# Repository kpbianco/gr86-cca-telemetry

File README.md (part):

# CCA Telemetry (GR86 / BRZ Gen2)

CCA Telemetry is a RaceChrono-compatible telemetry stack for the Toyota GR86 / Subaru BRZ (ZN8/ZD8) platform. An ESP32-S3 collects CAN, GPS, and auxiliary analog data, then streams it over Bluetooth Low Energy using RaceChrono's DIY device profile. The codebase is designed for track reliability: aggressive BLE reconnects, TWAI burst handling, persistent configuration, and configurable CAN filtering are all built in.

Hardware bring-up (CAN transceiver wiring, GPS, OLEDs, etc.) is intentionally out of scope here—assume those pieces are already handled. This repository focuses on the firmware, documentation, and validation artifacts you need to build, modify, and deploy the project.

## What this guide covers

* **End-to-end bring-up.** The “Track-day bring-up checklist” walks from flashing through wiring, BLE pairing, and pre-session validation so even a first-time CAN user can connect, configure, and verify the module before heading out.【F:README.md†L46-L125】
* **Subsystem deep dives.** “Firmware architecture,” “Oil pressure channel & calibration,” and the PID-map sections explain how each feature works (CAN ingest, BLE, GPS/PPS, oil analog path, pidmaps) and point directly to the source files for further hacking.【F:README.md†L77-L150】【F:README.md†L206-L213】
* **Runtime operations.** The Serial CLI reference documents every SHOW/PROFILE/ALLOW/FIL/TOKEN/RATE/SAVE command so you can administer the device without reflashing once it is installed in the car.【F:README.md†L214-L244】
* **RaceChrono & filtering workflows.** The RaceChrono integration, `.fil` ingestion walkthrough, and pidmap cloning guide teach you how to curate channels from the phone or at compile time, keeping CAN/BLE bandwidth under control.【F:README.md†L131-L150】【F:README.md†L180-L213】
* **Diagnostics & recovery.** LED pin/pattern tables, the troubleshooting checklist, and persistent-configuration guidance translate firmware counters into hands-on fixes at the car so you can recover from CAN, BLE, GPS, or oil faults mid-event.【F:README.md†L114-L130】【F:README.md†L123-L178】【F:README.md†L238-L244】

Together these sections document the full software feature set—from CAN filtering to RaceChrono streaming and oil calibration—so newcomers can treat the README as a production-ready operations guide.

## Release-ready polish

To make the repo publishable as an open-source reference design, every workflow called out in prior PRs is now paired with actionable guidance in this README:

* **Single source of truth.** The Track-day checklist, subsystem deep dives, CLI catalog, and RaceChrono workflows are all anchored to the implementation files they describe, so readers can jump from prose to code while auditing the feature set.
* **Operator focus.** Each runtime touch point—PID governance, GPS/PPS, oil calibration, RaceChrono filters, persistence—includes both “how it works” and “how to recover” instructions so someone new to CAN can confidently run the module at the track.
* **Debug-to-code breadcrumbs.** LED tables, SHOW/CAL output, and `.fil` logging now cite the handlers that emit those diagnostics, letting contributors trace symptoms back to the firmware without guesswork.

This section is the final assurance that the README stands alone as a production-ready operations manual: new users get the high-level tour at the top, the detailed workflows in the middle, and the debug/persistence references at the end without needing outside docs.

## Feature matrix & documentation coverage

| Feature / decision | Where it lives in code | Where to configure / operate it |
|--------------------|------------------------|----------------------------------|
| CAN burst ingestion, TWAI error recovery, PID throttling | `firmware/cca_telemetry.ino` main loop + TWAI handlers | *Firmware architecture → CAN ingestion & PID governance* and *Track-day bring-up checklist* describe how to wire and validate the bus before driving.【F:firmware/cca_telemetry.ino†L205-L235】【F:README.md†L23-L71】 |
| BLE transport, RaceChrono DIY profile, diagnostics notify | NimBLE setup in `firmware/cca_telemetry.ino` | *Track-day bring-up checklist → Pair with RaceChrono*, *RaceChrono integration*, and the troubleshooting bullets tie the LEDs, CLI, and `.fil` workflow together for new users.【F:firmware/cca_telemetry.ino†L89-L146】【F:README.md†L40-L73】【F:README.md†L120-L152】 |
| GPS + PPS time discipline | `firmware/src/gps_nmea.*`, PPS ISR in the sketch | *Firmware architecture → GPS & PPS discipline* plus the LED/troubleshooting tables walk through wiring, lock states, and debugging steps.【F:firmware/src/gps_nmea.cpp†L1-L210】【F:README.md†L75-L152】 |
| Oil pressure sampling, filtering, calibration, and CAN 0x710 publisher | Analog path in `firmware/cca_telemetry.ino` + `nvs_cfg.*` | *Track-day bring-up checklist*, *Oil pressure channel & calibration*, and the CLI section spell out how to hook up sensors, capture endpoints, and stream the data.【F:firmware/cca_telemetry.ino†L755-L807】【F:README.md†L33-L58】【F:README.md†L190-L225】 |
| PID maps, whitelist/deny list, divider overrides, `.fil` ingestion | `firmware/pidmaps/*.h`, filter characteristic handlers | *Creating your own PID map* and *Allowing extra PIDs from RaceChrono filter files* provide both build-time and runtime workflows, while CLI commands (`PROFILE`, `ALLOW`, `DENY`, `FIL VERBOSE`, `TOKEN`) are cataloged in the Serial CLI reference.【F:firmware/pidmaps/gr86_2022.h†L1-L162】【F:firmware/cca_telemetry.ino†L1360-L1465】【F:README.md†L152-L210】 |
| Persistent configuration and recovery | `firmware/src/nvs_cfg.*` | *Configuration workflow* and *Serial CLI → Persistence & recovery* explain how to edit defaults, capture runtime tweaks, and reset misconfigurations without reflashing.【F:firmware/src/nvs_cfg.cpp†L1-L116】【F:README.md†L171-L199】 |
| LED pinout, blink dictionary, scheduler hooks | `firmware/src/led_status.*`, `firmware/src/sched.hpp` | *Status LED + scheduler* table plus the troubleshooting checklist let a first-time CAN user translate physical indicators into next steps at the car.【F:firmware/src/led_status.cpp†L11-L192】【F:README.md†L92-L152】 |
| Build & flash repeatability | Arduino CLI/IDE instructions in this repo | *Building and flashing* covers both GUI and headless flows; the *Maintenance checklist* calls out regression tests to keep the repo production-ready.【F:README.md†L210-L266】 |

This matrix ensures every subsystem that ships in the firmware is paired with an operator-facing doc section, so a new builder can move from flashing through troubleshooting without chasing external resources.

## Repository layout

```
.
├── README.md                ← You're here
├── docs/                    ← RaceChrono presets and user-facing docs
├── firmware/
│   ├── cca_telemetry.ino    ← Main Arduino sketch for the ESP32-S3
│   ├── config.h             ← User-editable build-time configuration
│   ├── pidmaps/             ← CAN whitelist & scaling definitions
│   └── src/                 ← Reusable C++ helpers (GPS parser, NVS config, LEDs, scheduler)
├── libraries/               ← Vendored Arduino dependencies
```

## Track-day bring-up checklist

These steps walk a first-time CAN user from a blank ESP32-S3 dev module to a working RaceChrono feed. Each item links back to the source so you know which files implement the behavior you are validating.

### 1. Flash and configure the firmware

1. Install the ESP32 support package inside the Arduino IDE or CLI and select the **ESP32S3 Dev Module** target, matching the board the sketch was written for.【F:firmware/cca_telemetry.ino†L1-L20】
2. Open `firmware/config.h` and set the user-facing knobs—`DEVICE_NAME`, `DEFAULT_UPDATE_RATE_DIVIDER`, PPS input (`GPS_PPS_GPIO`), CAN baud, and `ACTIVE_PID_MAP`. These constants gate BLE discovery, the CAN throttle default, and whether PPS disciplining is enabled at boot.【F:firmware/config.h†L4-L27】
3. Build and flash `firmware/cca_telemetry.ino` using the instructions later in this README. The sketch pulls in the vendored libraries automatically, so no additional dependency fetch is required beyond what lives in `libraries/`.【F:firmware/cca_telemetry.ino†L21-L57】
4. Connect to the USB serial console at 115200 8N1, hit enter to reveal the prompt, then run `SHOW CFG` to confirm the compiled defaults (BLE name, profile mode, dividers) match what you edited before heading to the car.【F:firmware/cca_telemetry.ino†L2370-L2395】【F:firmware/cca_telemetry.ino†L3400-L3409】

### 2. Wire and power the module

1. Tie the SN65HVD230 (or equivalent) transceiver’s TXD/RXD pins to `GPIO5`/`GPIO4`, then hook its CANH/CANL pins into the car’s 500 kbps high-speed bus; the firmware leaves the TWAI controller in listen mode until it sees valid frames so you can verify the connection on the bench first.【F:firmware/cca_telemetry.ino†L76-L82】【F:firmware/config.h†L20-L21】
2. Wire your GPS puck to UART1 (`GPIO18` ← GPS TX, `GPIO17` → GPS RX) and land an optional PPS input on `GPIO16` if you want nanosecond-level lap timing—the PPS ISR and slew limiter are already enabled as soon as `GPS_PPS_GPIO` is ≥ 0.【F:firmware/cca_telemetry.ino†L80-L109】【F:firmware/config.h†L11-L15】
3. Route the analog oil-pressure sender into `GPIO1/ADC1_CH0`. The firmware samples, filters, and publishes it on virtual CAN ID `0x710`, so all you need to do trackside is capture two calibration points with the CLI after plumbing the sensor.【F:firmware/cca_telemetry.ino†L5-L7】【F:firmware/cca_telemetry.ino†L755-L775】
4. Land the status LEDs on the default pins (`GPIO46`, `GPIO6`, `GPIO7`, `GPIO8`, `GPIO10`, and `GPIO3`) or adjust the macros in `firmware/src/led_status.h` if your harness is different. The table later in this README explains every blink pattern you will see once the car powers the unit.【F:firmware/src/led_status.h†L6-L32】【F:firmware/cca_telemetry.ino†L1368-L1373】

### 3. Pair with RaceChrono and feed channels

1. Power the car or bench supply so the ESP32 starts advertising under the `DEVICE_NAME` you configured. RaceChrono will discover the DIY service (`0x1FF8`) plus the CAN, GPS, GPS-time, filter, and diagnostics characteristics defined in the sketch.【F:firmware/cca_telemetry.ino†L89-L95】
2. Import `docs/racechrono_preset.md` into RaceChrono to create ready-made channels for every GR86/BRZ PID in the curated allow-list, including the synthetic oil frame on `0x710`. This saves you from typing scaling equations on the phone.【F:docs/racechrono_preset.md†L1-L68】
3. If you need to add or remove CAN IDs directly from your phone, issue a `TOKEN <hex8>` over serial and then push a `.fil` file from RaceChrono’s *Manage filters* UI. Each command in the file becomes an ALLOW/DENY write on characteristic `0x0002`, which the firmware authenticates with the token before applying it to the runtime map.【F:firmware/cca_telemetry.ino†L1360-L1465】【F:firmware/cca_telemetry.ino†L3613-L3647】
4. Finish the pairing pass by checking `SHOW MAP` / `SHOW DENY` and the BLE diagnostics characteristic (`0x0005`) so you know the RaceChrono UI and the firmware are in sync before the session.【F:firmware/cca_telemetry.ino†L3345-L3505】【F:firmware/cca_telemetry.ino†L867-L920】

### 4. Validate data flow and hit the track

1. Watch the LED bank: solid power LED plus pulsing CAN/GPS LEDs indicate the car is broadcasting and GPS sentences are flowing, while the SYS LED warns about BLE throttling so you can bump dividers before packets drop.【F:firmware/src/led_status.h†L6-L32】【F:firmware/cca_telemetry.ino†L3732-L3879】
2. Use `SHOW STATS` after a shakedown lap to confirm there are no CAN timeouts, TWAI restarts, or BLE notify drops. The counters cover every subsystem mentioned earlier in this README.【F:firmware/cca_telemetry.ino†L3411-L3438】
3. Run `CAL SHOW`, `SHOW CFG`, and `RATE` to double-check that oil calibration, broadcast cadence, and profile mode match what you expect before logging laps; save any runtime tweaks so they persist across pit cycles.【F:firmware/cca_telemetry.ino†L3507-L3575】【F:firmware/cca_telemetry.ino†L3566-L3575】【F:firmware/cca_telemetry.ino†L782-L807】

## Firmware architecture

The sketch in `firmware/cca_telemetry.ino` orchestrates several subsystems:

* **CAN ingestion** – `ESP32-TWAI-CAN` runs the ESP32's native TWAI controller in RX burst mode. PID throttling keeps BLE bandwidth under control while the `pidmaps` whitelist ensures only RaceChrono-ready signals are forwarded.
* **BLE transport** – `NimBLE-Arduino` implements the RaceChrono DIY profile (service `0x1FF8`). Notifications are rate-limited with an adaptive governor, reconnection restarts advertisers instead of destroying the controller, and diagnostic counters identify congestion/backpressure.
* **GPS & PPS discipline** – `firmware/src/gps_nmea.*` parses RMC/GGA sentences and disciplines system time to an external PPS input with slew limiting.
* **Persistent configuration** – `firmware/src/nvs_cfg.*` stores calibration data (analog dividers, device profile, etc.) in NVS so tweaks survive power cycles.
* **Status LED + scheduler** – `firmware/src/led_status.*` and `firmware/src/sched.hpp` provide non-blocking indicators and lightweight cooperative task scheduling for housekeeping loops.
* **RaceChrono mapping** – `firmware/pidmaps/` encapsulates CAN scaling/units per signal. `config.h` selects the active table and exposes knobs such as BLE device name, update dividers, and analog calibration constants.

### Subsystem deep dive

#### CAN ingestion and PID governance

The CAN stack configures TWAI alerts for RX queue overruns, bus-off, arbitration loss, and other critical faults, then polls those counters each second to decide when to restart the controller or surface diagnostic frames back to RaceChrono.【F:firmware/cca_telemetry.ino†L205-L235】 Above that, the `pidmaps` layer predefines the GR86/BRZ whitelist plus default per-ID dividers and lets the CLI flip between strict allow-list streaming (`PROFILE ON`) or a sniff-all fall-through that still honors the runtime deny list.【F:firmware/pidmaps/gr86_2022.h†L9-L118】【F:firmware/cca_telemetry.ino†L718-L865】 Custom divider overrides are persisted and applied on boot so you can bump individual CAN IDs without recompiling, and the same bookkeeping powers `SHOW MAP`, `ALLOW`, and `DENY` in the serial console.【F:firmware/cca_telemetry.ino†L712-L865】【F:firmware/cca_telemetry.ino†L3345-L3505】

**Whitelist, blacklist, and dividers.** Each entry in `firmware/pidmaps/*.h` carries a target RaceChrono channel plus a default divider, meaning “forward one in every _N_ frames for this CAN ID.” Lower dividers increase BLE load; higher ones conserve bandwidth for low-value or high-frequency signals. `PROFILE ON` enforces this whitelist (only IDs present in the map are forwarded) while `PROFILE OFF` switches to “sniff everything” and relies on the deny list to suppress noisy IDs. `ALLOW <pid> <div>` temporarily whitelists additional IDs with their own dividers, whereas `DENY <pid>` forces the firmware to drop that ID even if the profile is off or the ID appears in the static map. Both overrides are stored in NVS via `SAVE` so trackside experiments persist across reboots.【F:firmware/cca_telemetry.ino†L3341-L3609】

#### BLE transport and congestion control

`NimBLE-Arduino` exposes the full DIY profile (CAN, filter, GPS, GPS time, and diagnostics characteristics) and negotiates aggressive 7.5–15 ms connection intervals to keep RaceChrono synced.【F:firmware/cca_telemetry.ino†L275-L357】 A moving-average notify governor tracks bytes-per-second, clamps burst size, and progressively backs off when congestion or ATT errors show up, with event counters logged through `SHOW STATS` and the diagnostics characteristic so you know whether BLE or CAN is the bottleneck.【F:firmware/cca_telemetry.ino†L139-L174】【F:firmware/cca_telemetry.ino†L867-L920】 The reconnection path restarts advertisers and reapplies MTU sizing automatically, so unplugging power or losing the phone link no longer wedges the NimBLE host.【F:firmware/cca_telemetry.ino†L301-L357】

#### GPS and PPS discipline

`gps_nmea.cpp` parses both RMC and GGA sentences, clamps checksum errors, and normalizes latitude/longitude/altitude fields, while the main sketch tracks the GPS init state machine (autobaud probing, fallback timers, and periodic notify cadence).【F:firmware/src/gps_nmea.cpp†L1-L121】【F:firmware/src/gps_nmea.cpp†L123-L198】【F:firmware/cca_telemetry.ino†L237-L274】 When a PPS input is wired, the ISR debounces the pulse, estimates drift, and slews the system clock by ±2 ms/second to keep RaceChrono’s GPS and CAN timestamps aligned, which dramatically reduces lap interpolation error.【F:firmware/cca_telemetry.ino†L176-L188】

#### Persistent configuration and CLI tie-in

The `nvs_cfg` helpers serialize oil calibration voltages, versioning, and CRCs into the `cca_cfg` namespace so even power-cycled cars retain the analog slope you captured with `CAL` commands.【F:firmware/src/nvs_cfg.cpp†L1-L75】 Raw blobs can be inspected with `CAL SHOW`, and the same module exposes guard rails (finite, monotonic voltages) to keep corrupt data from applying at boot.【F:firmware/src/nvs_cfg.cpp†L76-L116】 In addition to analog endpoints, NVS stores PID divider overrides, custom oil broadcast rates, FIL tokens, and the profile bit so the CLI “SAVE / LOAD / RESETCFG” workflow mirrors what’s burned into flash.【F:firmware/cca_telemetry.ino†L782-L865】【F:firmware/cca_telemetry.ino†L3650-L3674】

#### Status LED + scheduler

`led_status.*` defines six independent channels (power, BLE, CAN, GPS, SYS, oil) with per-pin polarity, a library of blink/pulse patterns, and a tiny state machine that updates the GPIOs without blocking other tasks.【F:firmware/src/led_status.cpp†L11-L192】 Time-sliced housekeeping loops use the `every()` helper in `sched.hpp` to run at deterministic cadences (GPS notify, CAN diagnostics, oil broadcasts) even when other work momentarily stalls the main loop.【F:firmware/src/sched.hpp†L5-L23】

**Pinout and debug patterns.** The default harness routes the LEDs to the following ESP32-S3 pins (active high unless the macros in `led_status.h` are flipped). Use the table to translate each blink or pulse into a subsystem status when debugging at the car.【F:firmware/src/led_status.h†L6-L53】【F:firmware/cca_telemetry.ino†L1368-L1373】【F:firmware/cca_telemetry.ino†L3740-L3887】

| LED | ESP32-S3 GPIO | Patterns & meaning |
|-----|---------------|---------------------|
| Power | `GPIO46` | Turns solid immediately after `setup()` runs so you know the MCU left ROM boot and the scheduler/housekeeping loops are alive.【F:firmware/src/led_status.h†L6-L22】【F:firmware/cca_telemetry.ino†L2370-L2384】 |
| BLE | `GPIO6` | Fast blink while advertising/awaiting RaceChrono, solid once a BLE link is up, and off once RaceChrono disconnects so you can instantly spot pairing issues.【F:firmware/src/led_status.h†L6-L24】【F:firmware/cca_telemetry.ino†L1368-L1373】 |
| CAN | `GPIO7` | Slow blink means the TWAI driver is up but no recent frames have been seen, a double pulse every 2 s indicates live CAN traffic, and solid means the reader is running but has gone >1 s without a packet (check wiring or ignition).【F:firmware/src/led_status.h†L6-L26】【F:firmware/cca_telemetry.ino†L3732-L3744】 |
| GPS | `GPIO8` | Slow blink while waiting on UART data, solid when NMEA sentences are flowing, and triple pulses every two seconds once valid RMC fixes are locking timestamps to PPS.【F:firmware/src/led_status.h†L6-L28】【F:firmware/cca_telemetry.ino†L3860-L3875】 |
| SYS | `GPIO10` | Off during normal operation; switches to a slow blink whenever the BLE governor clamps notifications or the burst budget is exhausted, highlighting congestion before packets drop.【F:firmware/src/led_status.h†L6-L30】【F:firmware/cca_telemetry.ino†L3778-L3879】 |
| Oil | `GPIO3` | Solid = calibrated sensor in range; fast blink = ADC sees a short to ground; double pulse every 2 s = open harness; slow blink = voltage out of range but not a hard fault, matching the fault bits that go out on CAN `0x710`.【F:firmware/src/led_status.h†L6-L32】【F:firmware/cca_telemetry.ino†L3838-L3849】 |

## Troubleshooting checklist

* **No CAN frames** – Verify the CAN LED is double-pulsing; if it is solid or dark, check the SN65 wiring on `GPIO5/4` and make sure the bus really is at 500 kbps, then run `SHOW STATS` to confirm there are no TWAI restarts or RX timeouts being logged.【F:firmware/cca_telemetry.ino†L76-L82】【F:firmware/config.h†L20-L21】【F:firmware/cca_telemetry.ino†L3411-L3438】
* **BLE congestion** – A blinking SYS LED means the notify governor is clamping bursts; inspect the diagnostics characteristic (`0x0005`) and `SHOW STATS` counters, then raise the per-PID dividers or disable noisy IDs via `DENY`/`ALLOW`/`PROFILE` until the clamp counter stabilizes.【F:firmware/src/led_status.h†L6-L30】【F:firmware/cca_telemetry.ino†L867-L920】【F:firmware/cca_telemetry.ino†L3341-L3609】
* **GPS not locking** – The GPS LED should switch from slow blink to solid once UART sentences arrive and to triple pulses when PPS discipline is active; if it stays dark, confirm the UART pins (`GPIO18/17`) and PPS input (`GPIO16`) match your harness and recheck the GPS baud/autobaud logic in the console output.【F:firmware/cca_telemetry.ino†L80-L188】【F:firmware/config.h†L11-L15】【F:firmware/src/led_status.h†L6-L28】
* **Oil channel faults** – Combine the oil LED pattern with `CAL SHOW` output to see whether you are tripping the open/short bits, broadcasting stale calibration endpoints, or simply exceeding the configured pressure range. `RATE` lets you slow the cadence if BLE saturation coincides with the faults.【F:firmware/cca_telemetry.ino†L3382-L3549】【F:firmware/cca_telemetry.ino†L3566-L3575】【F:firmware/src/led_status.h†L6-L32】
* **RaceChrono filters not applying** – Turn `FIL VERBOSE ON`, make sure the FIL token matches, and watch the serial console for ALLOW/DENY updates while the `.fil` file streams; the runtime state is always visible via `SHOW MAP` / `SHOW DENY` before you `SAVE`.【F:firmware/cca_telemetry.ino†L1360-L1465】【F:firmware/cca_telemetry.ino†L3345-L3655】

#### RaceChrono mapping & docs

`firmware/pidmaps/` centralizes the RaceChrono-facing whitelist, scaling equations, and default dividers so each CAN signal documents its frequency and equation in one place, and the `docs/racechrono_preset.md` file provides copy/paste RaceChrono channel definitions—including the virtual oil pressure frame—for anyone replicating the setup without reverse-engineering the CAN bus themselves.【F:firmware/pidmaps/gr86_2022.h†L9-L162】【F:docs/racechrono_preset.md†L1-L68】

### Creating your own PID map

1. **Copy the template.** Duplicate `firmware/pidmaps/gr86_2022.h`, keep the include to `pidmaps/pidmap_defs.h`, and rename the namespace/`MAP` constant to match your chassis so the compiler gets a unique `PidMapDefinition`. The header already shows how the whitelist helper, divider policy, and `RULES` array hang together.【F:firmware/pidmaps/pidmap_defs.h†L1-L24】【F:firmware/pidmaps/gr86_2022.h†L1-L106】
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
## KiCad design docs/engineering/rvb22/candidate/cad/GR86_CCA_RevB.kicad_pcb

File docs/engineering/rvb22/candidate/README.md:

# GR86 Rev B — I12 corrective engineering in progress

The upper PCB wing now carries the approved compact TranquilWorks TW artwork in one-color silkscreen. The U201 library antenna rule area is corrected from board-relative translation to local coordinates; the board keepout and all electrical geometry remain unchanged. All153 fitted references have model references;22 missing/broken entries receive dimensioned envelopes with explicit XY and height provenance. Native export coverage is now checked against all153 STEP assembly occurrences.

This is an intermediate checkpoint within the coordinated I12 revision. Thermal, foil/contact, complete connector envelopes and affected regressions remain in progress, as listed in verification/I12/REDLINE_FREEZE.json. Native reevaluation is pending; no release or zero-overall claim follows from these edits.

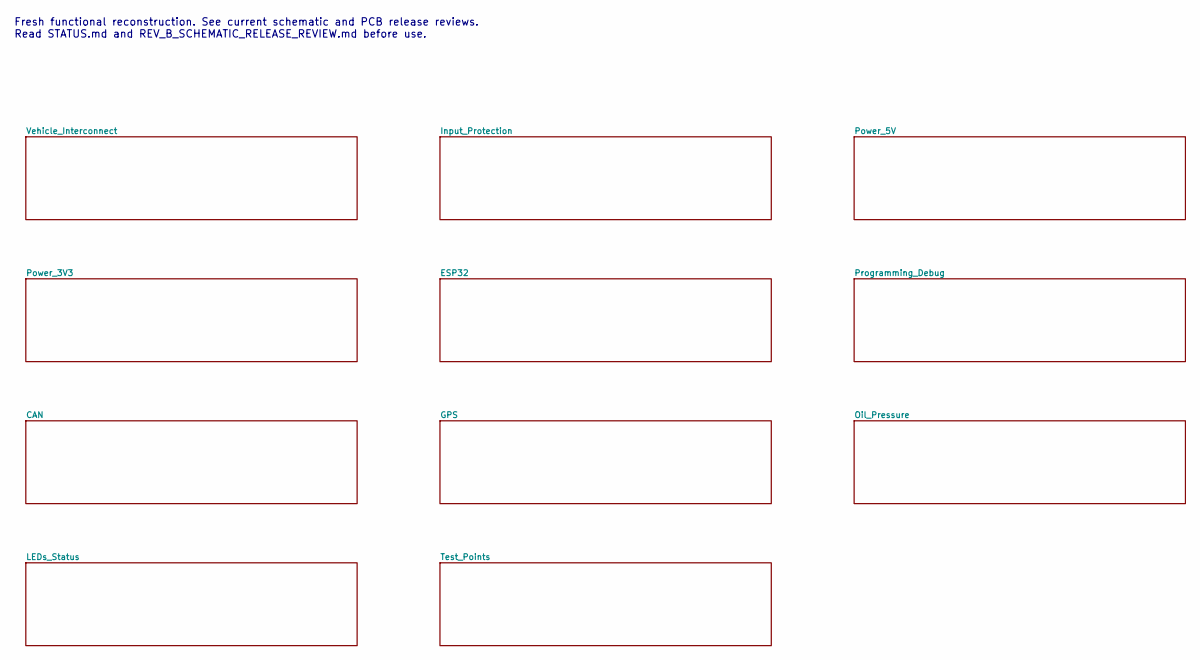
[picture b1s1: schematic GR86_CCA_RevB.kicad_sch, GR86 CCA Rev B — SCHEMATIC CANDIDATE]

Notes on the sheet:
Fresh functional reconstruction. See current schematic and PCB release reviews. Read STATUS.md and REV_B_SCHEMATIC_RELEASE_REVIEW.md before use.

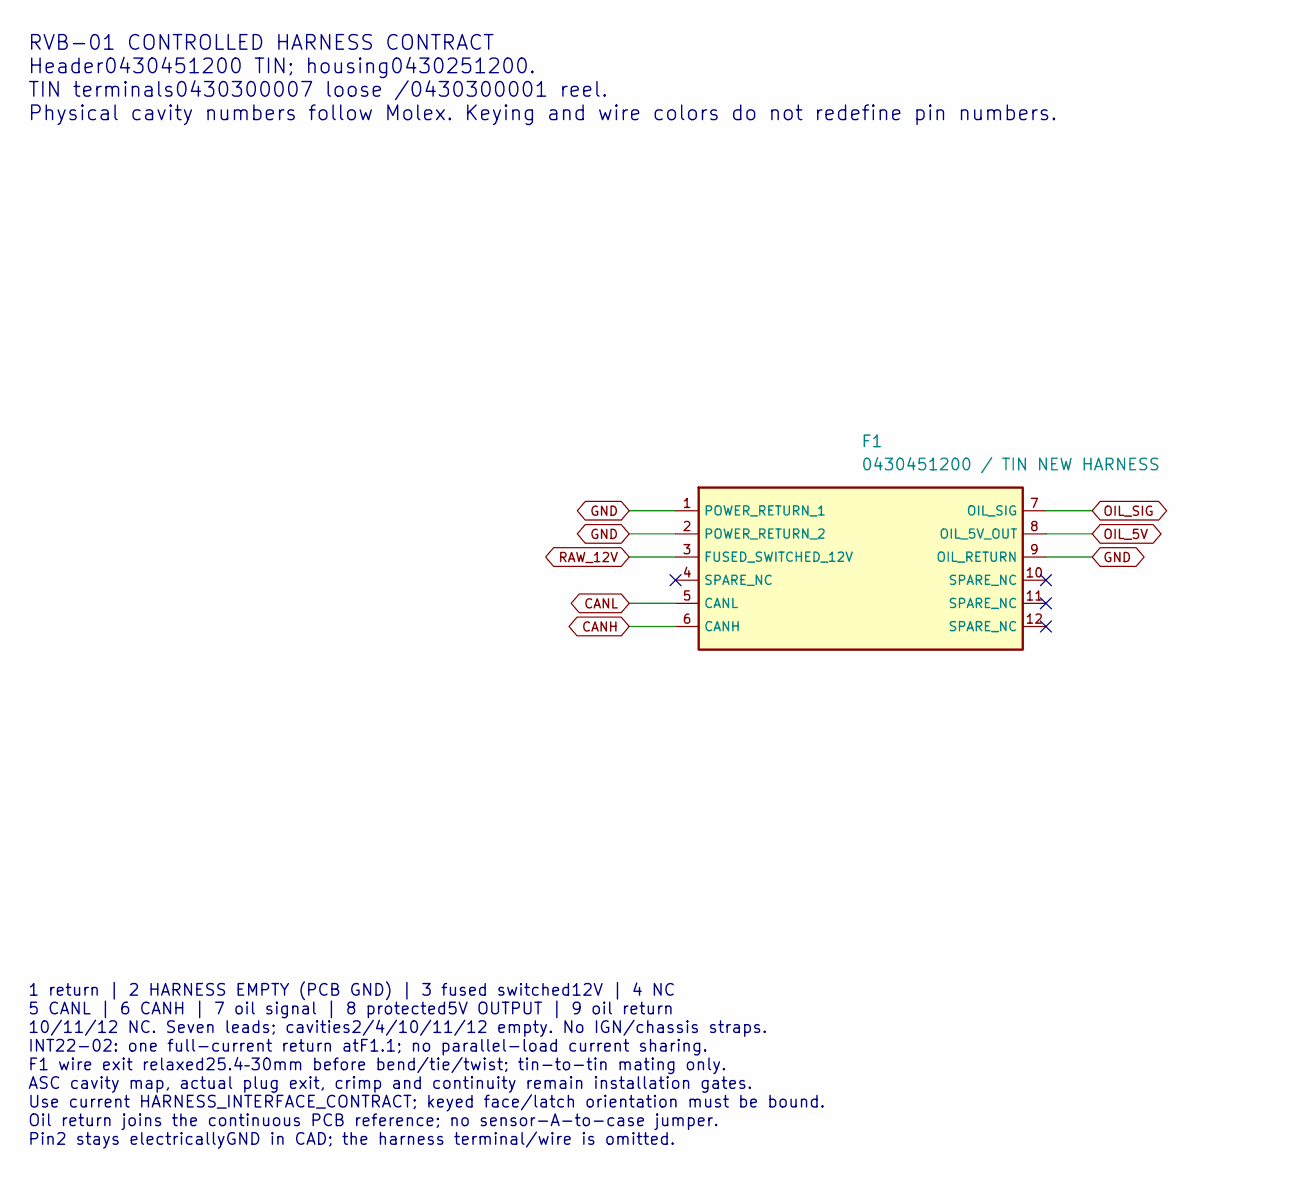
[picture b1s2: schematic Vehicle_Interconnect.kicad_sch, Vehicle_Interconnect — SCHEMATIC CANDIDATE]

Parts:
F1: 0430451200 / TIN NEW HARNESS; Molex_Micro-Fit_3.0_43045-1200_2x06_P3.00mm_Horizontal_RVB2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; MPN 0430451200; LCSC C277636

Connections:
CANH: F1.6 (CANH); also elsewhere on the board
CANL: F1.5 (CANL); also elsewhere on the board
GND: F1.1 (POWER_RETURN_1), F1.2 (POWER_RETURN_2), F1.9 (OIL_RETURN); also elsewhere on the board
OIL_5V: F1.8 (OIL_5V_OUT); also elsewhere on the board
OIL_SIG: F1.7 (OIL_SIG); also elsewhere on the board
RAW_12V: F1.3 (FUSED_SWITCHED_12V); also elsewhere on the board

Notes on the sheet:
RVB-01 CONTROLLED HARNESS CONTRACT Header0430451200 TIN; housing0430251200. TIN terminals0430300007 loose /0430300001 reel. Physical cavity numbers follow Molex. Keying and wire colors do not redefine pin numbers.
1 return | 2 HARNESS EMPTY (PCB GND) | 3 fused switched12V | 4 NC 5 CANL | 6 CANH | 7 oil signal | 8 protected5V OUTPUT | 9 oil return 10/11/12 NC. Seven leads; cavities2/4/10/11/12 empty. No IGN/chassis straps. INT22-02: one full-current return atF1.1; no parallel-load current sharing. F1 wire exi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

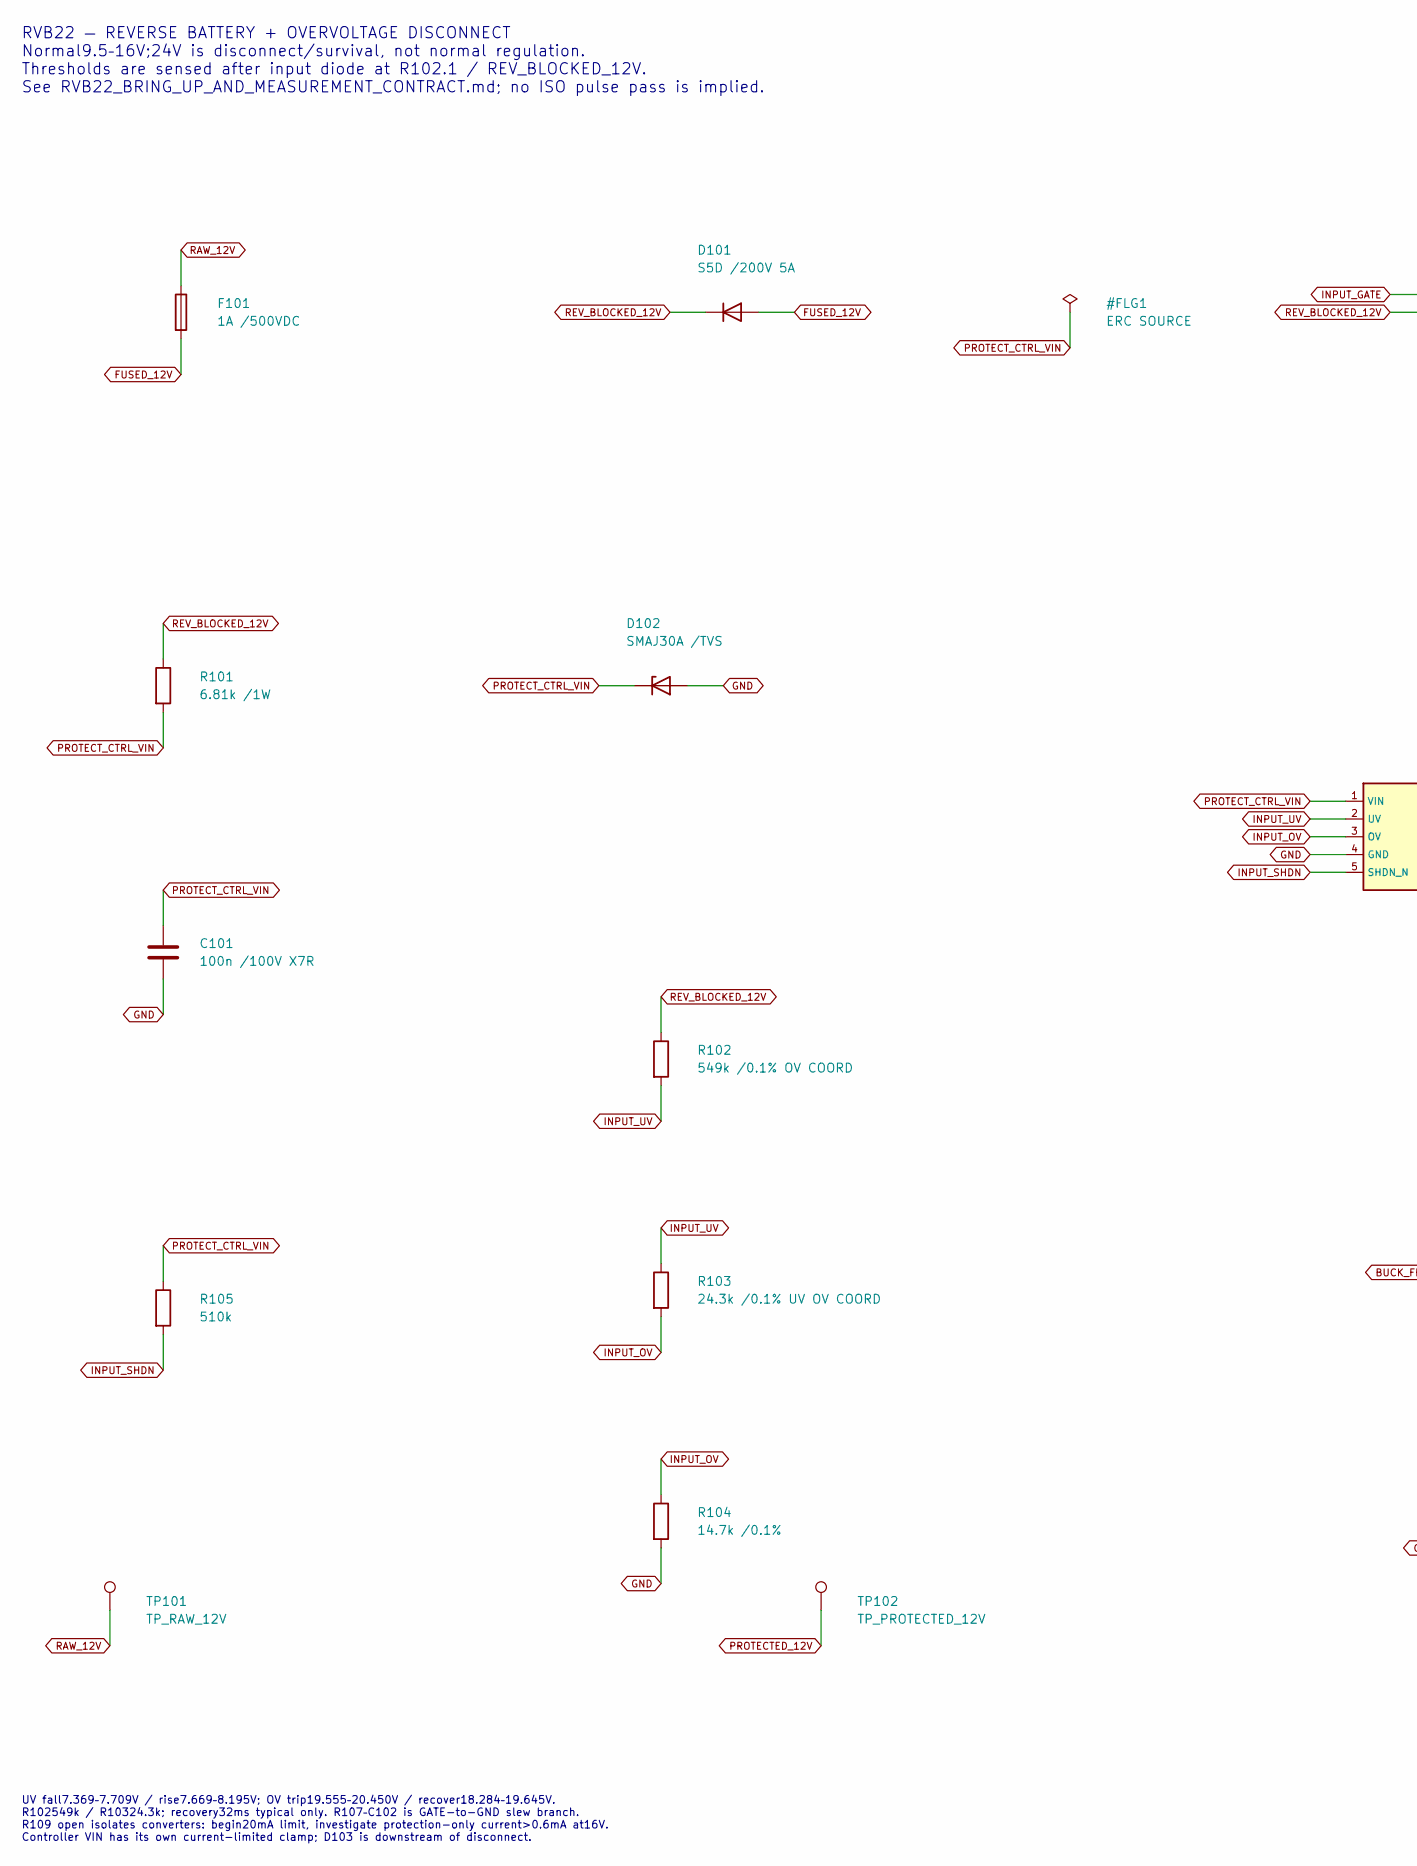
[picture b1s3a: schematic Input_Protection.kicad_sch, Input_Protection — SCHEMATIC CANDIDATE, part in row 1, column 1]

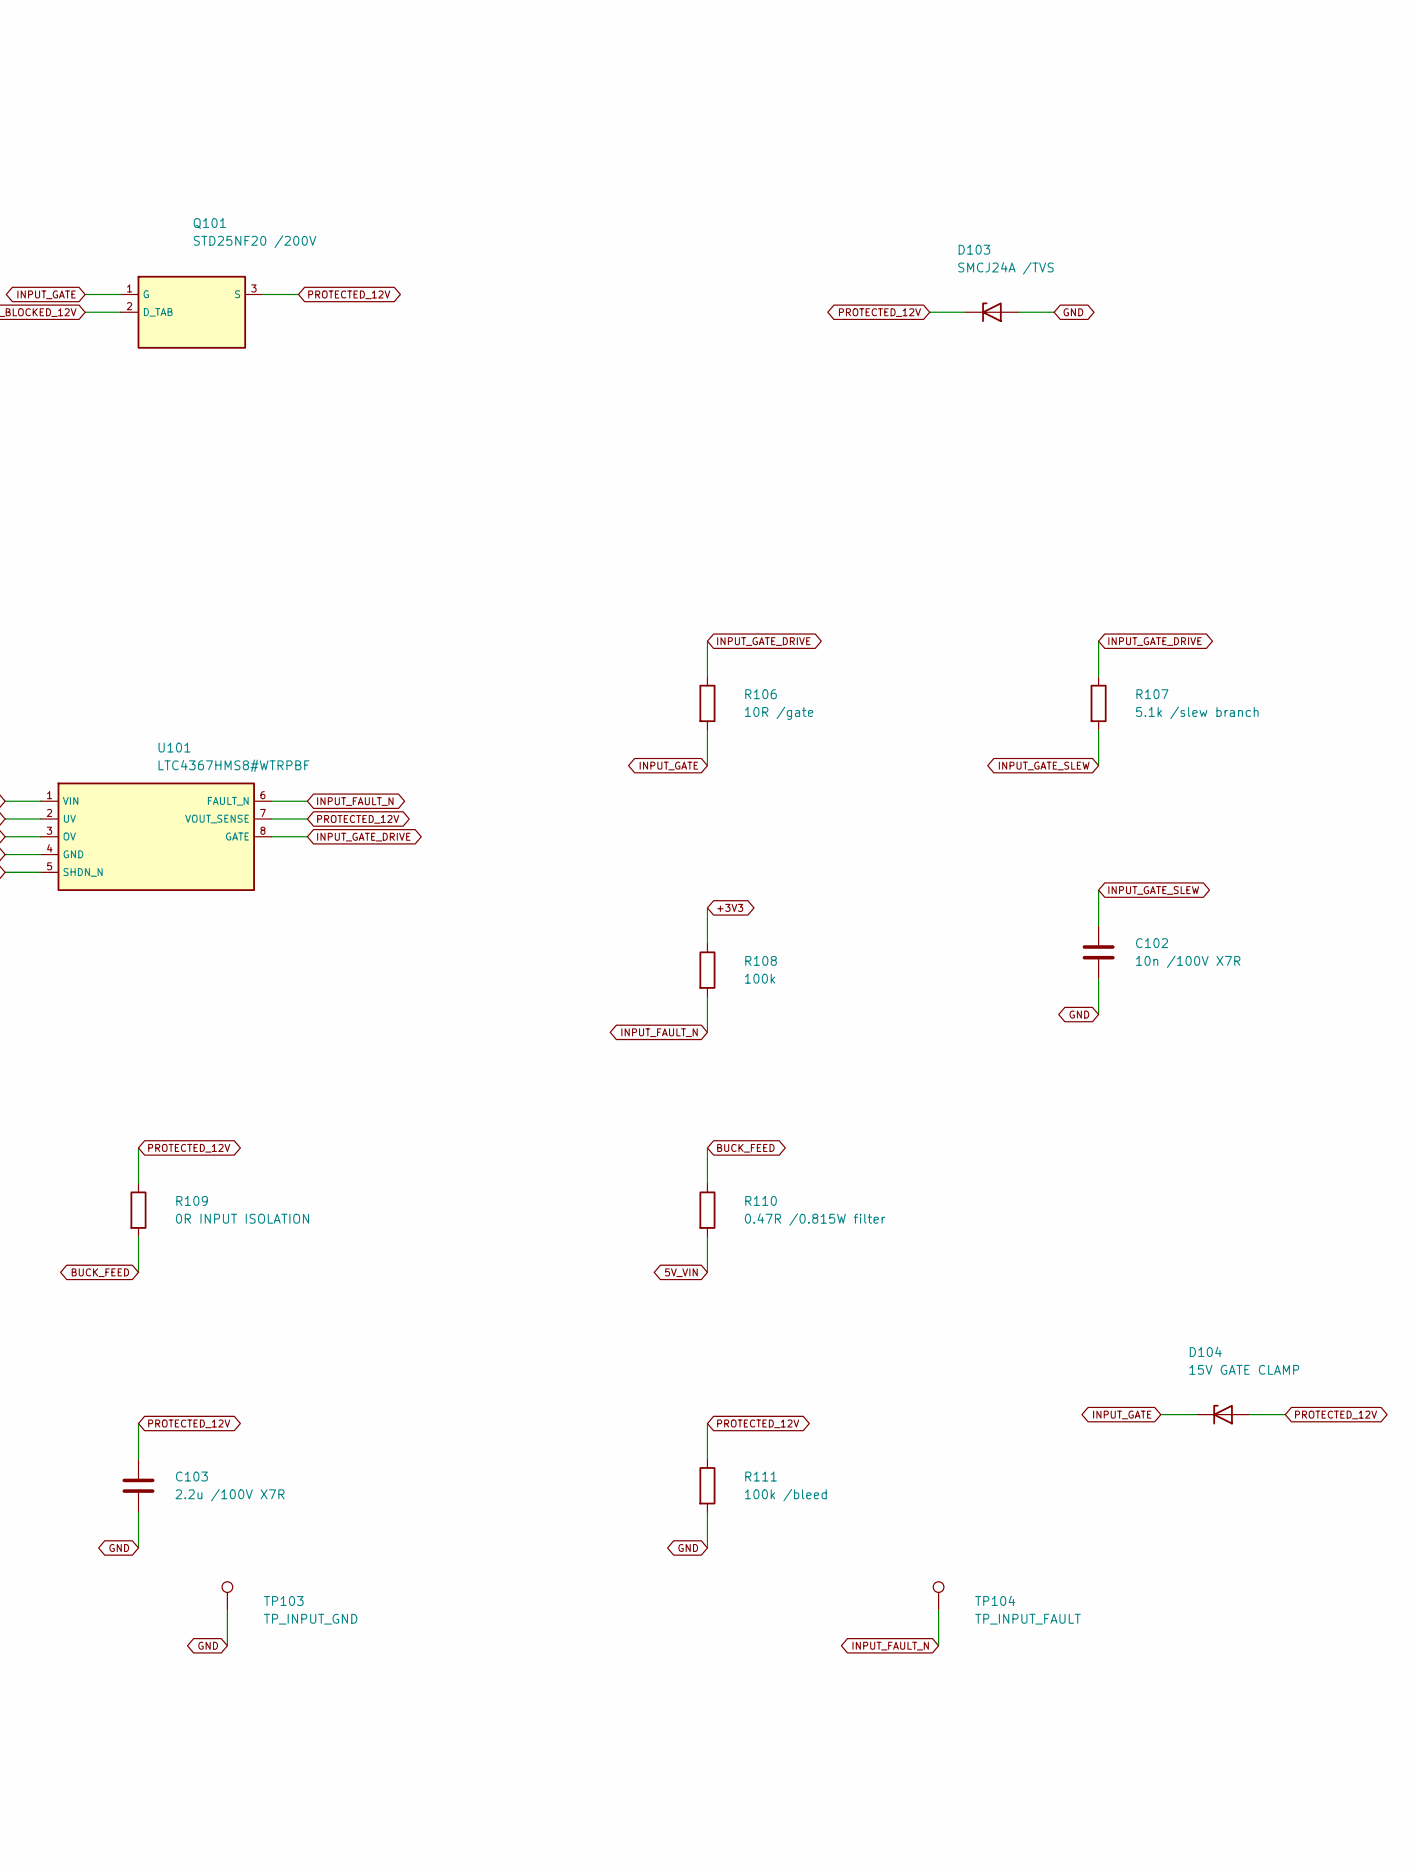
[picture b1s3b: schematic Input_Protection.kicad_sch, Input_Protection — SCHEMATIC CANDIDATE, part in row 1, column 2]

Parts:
C101: 100n /100V X7R; C_0805_2012Metric; MPN CGA4J2X7R2A104K125AA; LCSC C342919
C102: 10n /100V X7R; C_0603_1608Metric; MPN CGA3E2X7R2A103K080AE; LCSC C3858696
C103: 2.2u /100V X7R; C_1210_3225Metric; MPN CGA6N3X7R2A225K230AB; LCSC C342652
D101: S5D /200V 5A; D_SMC; MPN S5DHE3_A/H; LCSC C17442489
D102: SMAJ30A /TVS; D_SMA; MPN SMAJ30AHE3_A/H; LCSC C1978408
D103: SMCJ24A /TVS; D_SMC_RVB22_D103; MPN SMCJ24AHE3_A/H; LCSC C1981952
D104: 15V GATE CLAMP; D_SOD-123F; MPN BZT52H-B15-QX; LCSC C7507926
F101: 1A /500VDC; Fuse_Littelfuse-NANO2-885; MPN 0885001.DR; LCSC C2879865
Q101: STD25NF20 /200V; TO-252-2; MPN STD25NF20; LCSC C388326
R101: 6.81k /1W; R_2512_6332Metric; MPN CRCW25126K81FKEG; LCSC C4207450
R102: 549k /0.1% OV COORD; R_1206_3216Metric; MPN TNPW1206549KBEEA
R103: 24.3k /0.1% UV OV COORD; R_0603_1608Metric; MPN TNPW060324K3BEEA
R104: 14.7k /0.1%; R_0603_1608Metric; MPN ERA3AEB1472V; LCSC C2074591
R105: 510k; R_1206_3216Metric; MPN CRCW1206510KFKEA; LCSC C843859
R106: 10R /gate; R_0603_1608Metric; MPN CRCW060310R0FKEA; LCSC C844919
R107: 5.1k /slew branch; R_0603_1608Metric; MPN CRCW06035K10FKEA; LCSC C844933
R108: 100k; R_0603_1608Metric; MPN CRCW0603100KFKEA; LCSC C844916
R109: 0R INPUT ISOLATION; R_1206_3216Metric; MPN CRCW12060000Z0EA; LCSC C190124
R110: 0.47R /0.815W filter; R_2512_6332Metric; MPN WSL2512R4700FEA; LCSC C4273015
R111: 100k /bleed; R_1206_3216Metric; MPN CRCW1206100KFKEA; LCSC C844863
TP101: TP_RAW_12V; TestPoint_Pad_D1.5mm; MPN BARE PCB PAD
TP102: TP_PROTECTED_12V; TestPoint_Pad_D1.5mm; MPN BARE PCB PAD
TP103: TP_INPUT_GND; TestPoint_Pad_D1.5mm; MPN BARE PCB PAD
TP104: TP_INPUT_FAULT; TestPoint_Pad_D1.5mm; MPN BARE PCB PAD
U101: LTC4367HMS8#WTRPBF; MSOP-8_3x3mm_P0.65mm; MPN LTC4367HMS8#WTRPBF

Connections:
5V_VIN: R110.2; also elsewhere on the board
+3V3: R108.1; also elsewhere on the board
BUCK_FEED: R109.2, R110.1
FUSED_12V: D101.2 (A), F101.2
GND: C101.2, C102.2, C103.2, D102.2 (A), D103.2 (A), R104.2, R111.2, TP103.1, U101.4 (GND); also elsewhere on the board
INPUT_FAULT_N: R108.2, TP104.1, U101.6 (FAULT_N)
INPUT_GATE: D104.1 (K), Q101.1 (G), R106.2
INPUT_GATE_DRIVE: R106.1, R107.1, U101.8 (GATE)
INPUT_GATE_SLEW: C102.1, R107.2
INPUT_OV: R103.2, R104.1, U101.3 (OV)
INPUT_SHDN: R105.2, U101.5 (SHDN_N)
INPUT_UV: R102.2, R103.1, U101.2 (UV)
PROTECTED_12V: C103.1, D103.1 (K), D104.2 (A), Q101.3 (S), R109.1, R111.1, TP102.1, U101.7 (VOUT_SENSE)
PROTECT_CTRL_VIN: C101.1, D102.1 (K), R101.2, R105.1, U101.1 (VIN)
RAW_12V: F101.1, TP101.1; also elsewhere on the board
REV_BLOCKED_12V: D101.1 (K), Q101.2 (D_TAB), R101.1, R102.1

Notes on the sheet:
RVB22 — REVERSE BATTERY + OVERVOLTAGE DISCONNECT Normal9.5–16V;24V is disconnect/survival, not normal regulation. Thresholds are sensed after input diode at R102.1 / REV_BLOCKED_12V. See RVB22_BRING_UP_AND_MEASUREMENT_CONTRACT.md; no ISO pulse pass is implied.
UV fall7.369–7.709V / rise7.669–8.195V; OV trip19.555–20.450V / recover18.284–19.645V. R102549k / R10324.3k; recovery32ms typical only. R107–C102 is GATE-to-GND slew branch. R109 open isolates converters: begin20mA limit, investigate protection-only current>0.6mA at16V. Controller VIN has its own c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

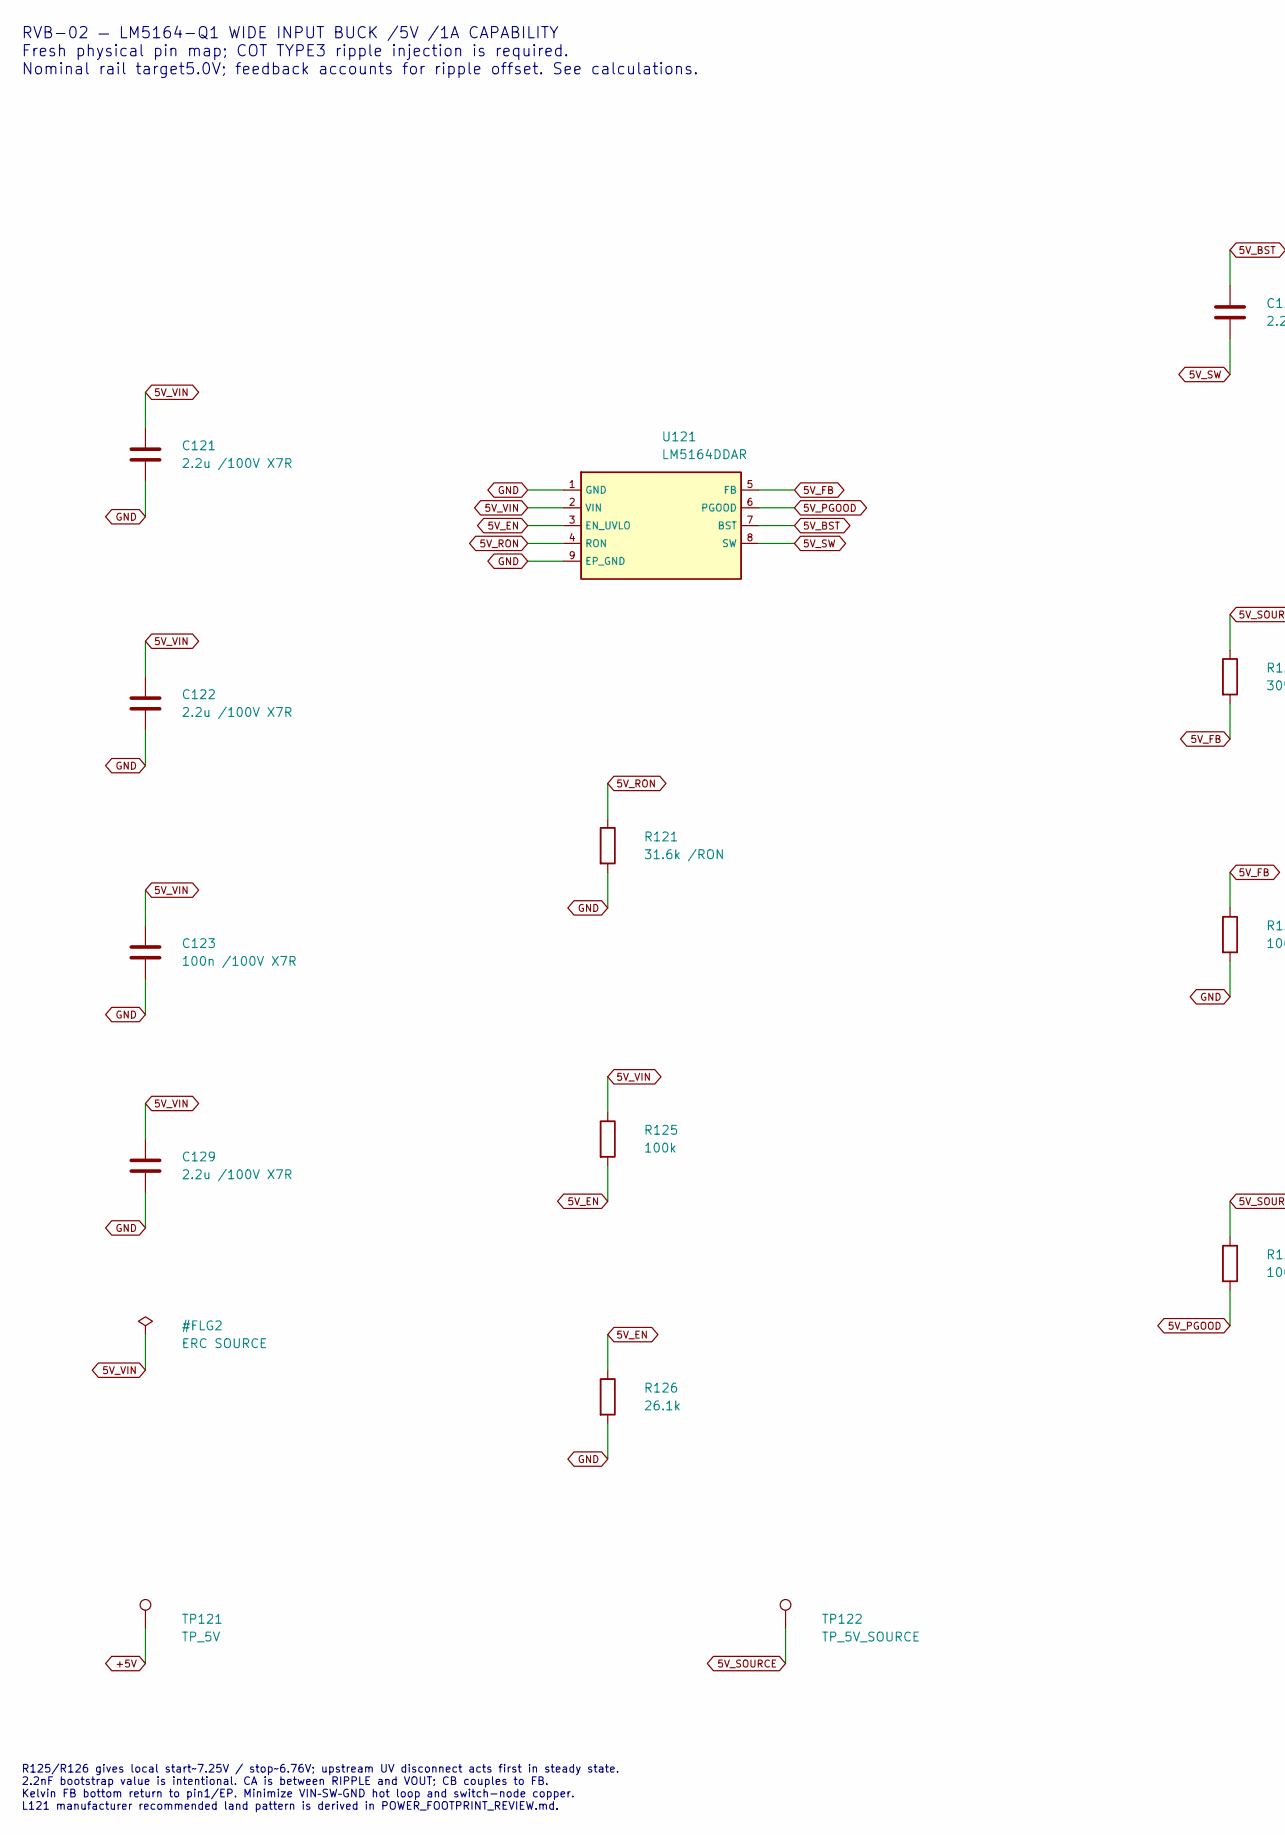
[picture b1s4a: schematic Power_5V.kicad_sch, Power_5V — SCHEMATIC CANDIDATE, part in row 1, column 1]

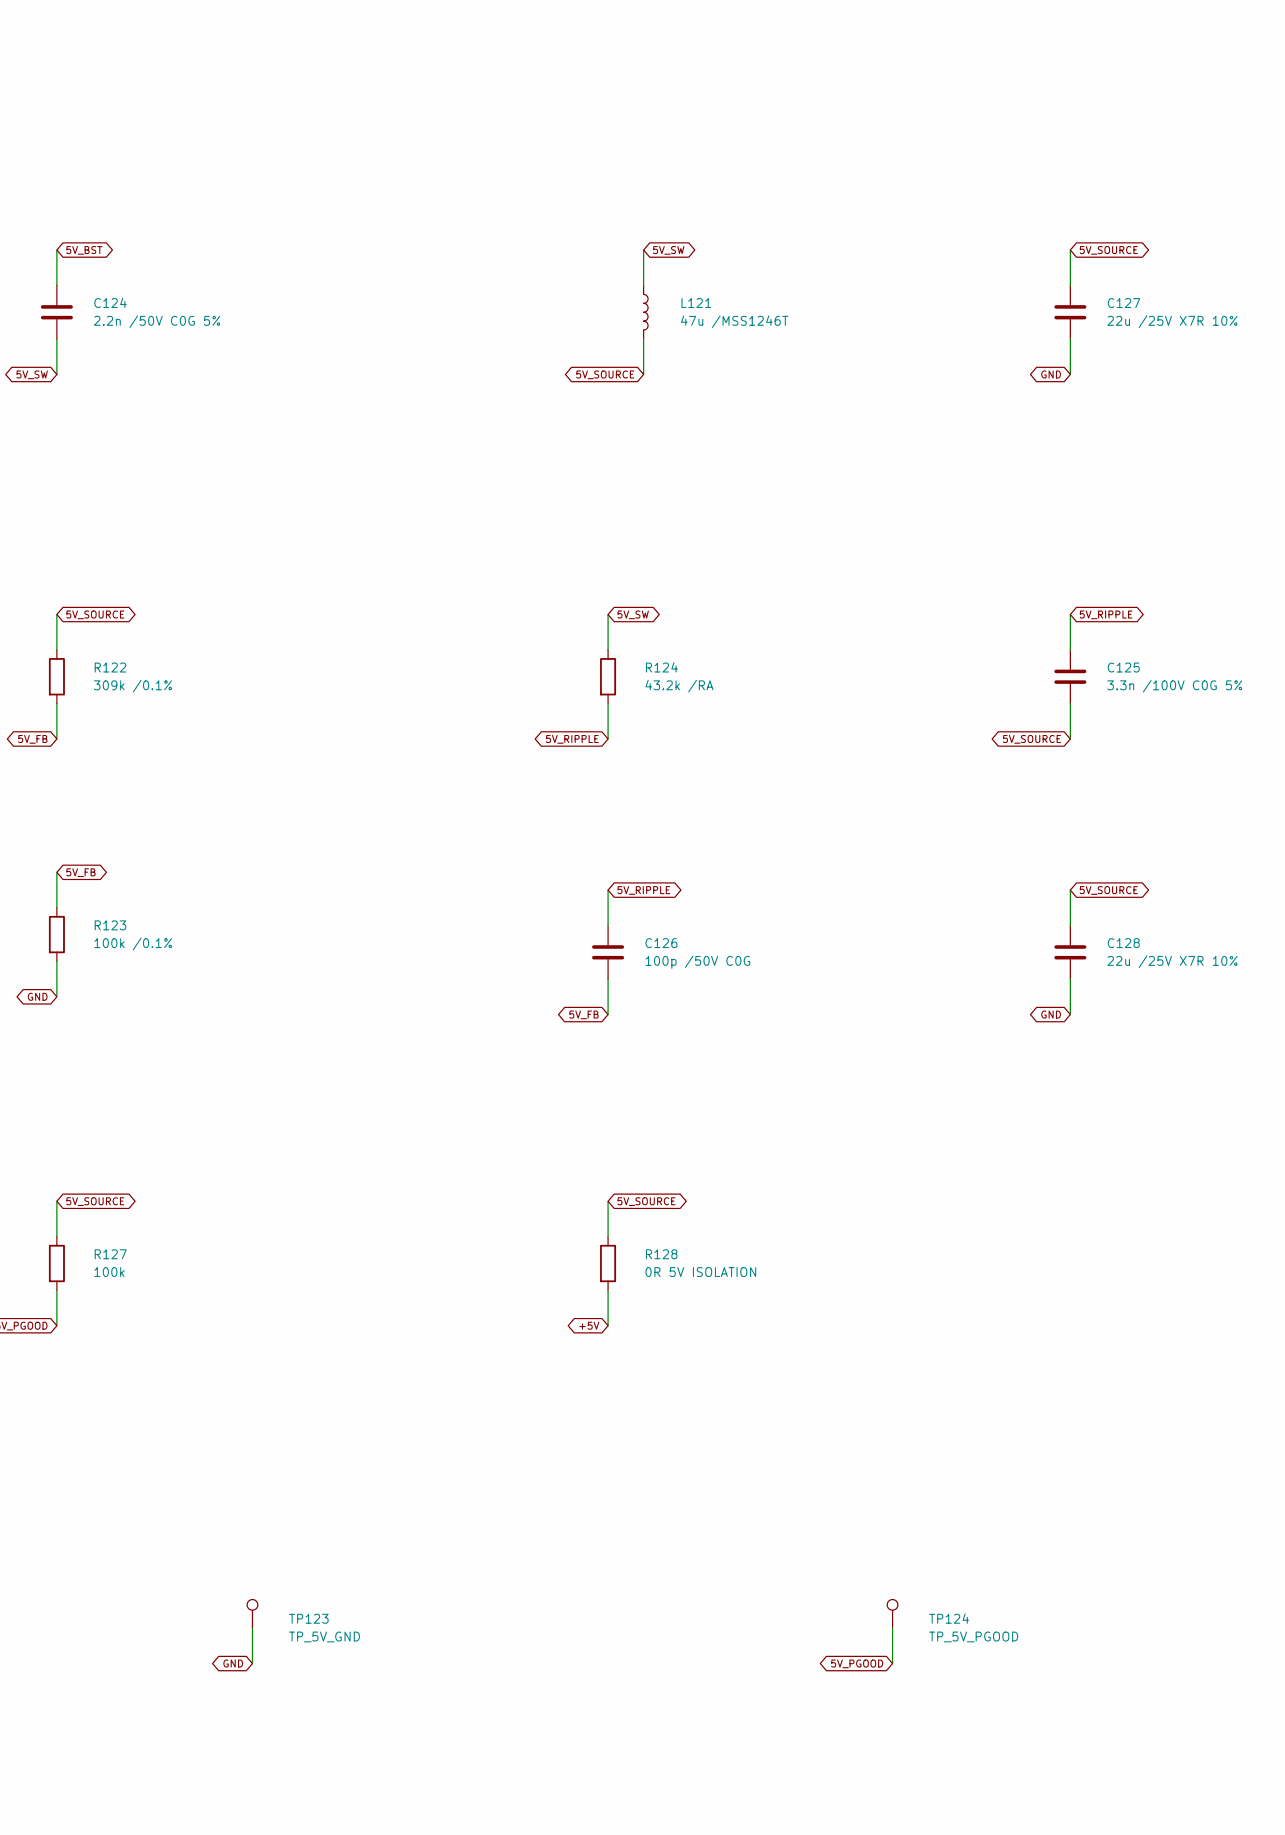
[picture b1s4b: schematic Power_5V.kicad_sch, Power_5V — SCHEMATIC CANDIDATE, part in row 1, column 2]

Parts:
C121, C122, C129: 2.2u /100V X7R; C_1210_3225Metric; MPN CGA6N3X7R2A225K230AB; LCSC C342652
C123: 100n /100V X7R; C_0805_2012Metric; MPN CGA4J2X7R2A104K125AA; LCSC C342919
C124: 2.2n /50V C0G 5%; C_0603_1608Metric; MPN CGA3E2C0G1H222J080AA; LCSC C2169200
C125: 3.3n /100V C0G 5%; C_0603_1608Metric; MPN CGA3E2C0G2A332J080AA; LCSC C2171993
C126: 100p /50V C0G; C_0603_1608Metric; MPN CGA3E2C0G1H101J080AA; LCSC C76709
C127, C128: 22u /25V X7R 10%; C_1210_3225Metric; MPN MCAST32MSB7226KPNA01; LCSC C5372271
L121: 47u /MSS1246T; Coilcraft_MSS1246T_12x12_RVB22_L121; MPN MSS1246T-473MLC
R121: 31.6k /RON; R_0603_1608Metric; MPN TNPW060331K6BEEA; LCSC C843870
R122: 309k /0.1%; R_0805_2012Metric; MPN TNPW0805309KBEEA; LCSC C1710754
R123: 100k /0.1%; R_0603_1608Metric; MPN TNPW0603100KBEEA; LCSC C844888
R124: 43.2k /RA; R_0603_1608Metric; MPN TNPW060343K2BEEA; LCSC C2089718
R125: 100k; R_1206_3216Metric; MPN CRCW1206100KFKEA; LCSC C844863
R126: 26.1k; R_0603_1608Metric; MPN ERA3AEB2612V; LCSC C491123
R127: 100k; R_0603_1608Metric; MPN CRCW0603100KFKEA; LCSC C844916
R128: 0R 5V ISOLATION; R_1206_3216Metric; MPN CRCW12060000Z0EA; LCSC C190124
TP121: TP_5V; TestPoint_Pad_D1.5mm; MPN BARE PCB PAD
TP122: TP_5V_SOURCE; TestPoint_Pad_D1.5mm; MPN BARE PCB PAD
TP123: TP_5V_GND; TestPoint_Pad_D1.5mm; MPN BARE PCB PAD
TP124: TP_5V_PGOOD; TestPoint_Pad_D1.5mm; MPN BARE PCB PAD
U121: LM5164DDAR; TI_DDA0008B_4214849B; MPN LM5164DDAR; LCSC C477928

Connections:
5V_BST: C124.1, U121.7 (BST)
5V_EN: R125.2, R126.1, U121.3 (EN_UVLO)
5V_FB: C126.2, R122.2, R123.1, U121.5 (FB)
5V_PGOOD: R127.2, TP124.1, U121.6 (PGOOD)
5V_RIPPLE: C125.1, C126.1, R124.2
5V_RON: R121.1, U121.4 (RON)
5V_SOURCE: C125.2, C127.1, C128.1, L121.2, R122.1, R127.1, R128.1, TP122.1
5V_SW: C124.2, L121.1, R124.1, U121.8 (SW)
5V_VIN: C121.1, C122.1, C123.1, C129.1, R125.1, U121.2 (VIN); also elsewhere on the board
+5V: R128.2, TP121.1; also elsewhere on the board
GND: C121.2, C122.2, C123.2, C127.2, C128.2, C129.2, R121.2, R123.2, R126.2, TP123.1, U121.1 (GND), U121.9 (EP_GND); also elsewhere on the board

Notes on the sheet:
RVB-02 — LM5164-Q1 WIDE INPUT BUCK /5V /1A CAPABILITY Fresh physical pin map; COT TYPE3 ripple injection is required. Nominal rail target5.0V; feedback accounts for ripple offset. See calculations.
R125/R126 gives local start~7.25V / stop~6.76V; upstream UV disconnect acts first in steady state. 2.2nF bootstrap value is intentional. CA is between RIPPLE and VOUT; CB couples to FB. Kelvin FB bottom return to pin1/EP. Minimize VIN–SW–GND hot loop and switch-node copper. L121 manufacturer recomm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

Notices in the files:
README.md:
License & acknowledgements:
This project builds on the open-source work of the ESP32, NimBLE, and RaceChrono communities. Please review the individual licenses inside `libraries/` before redistributing binaries.
